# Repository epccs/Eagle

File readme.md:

# Eagle Circuit Board Files

Eagle is software for Computer Aided Design (CAD) of printed circuit boards. Eagle was once owned by a company from Germany called Cadsoft but is now owned by Autodesk (Autocad).

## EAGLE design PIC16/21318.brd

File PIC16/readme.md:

[PIC16]

This folder has the Eagle files for the PIC16 board.

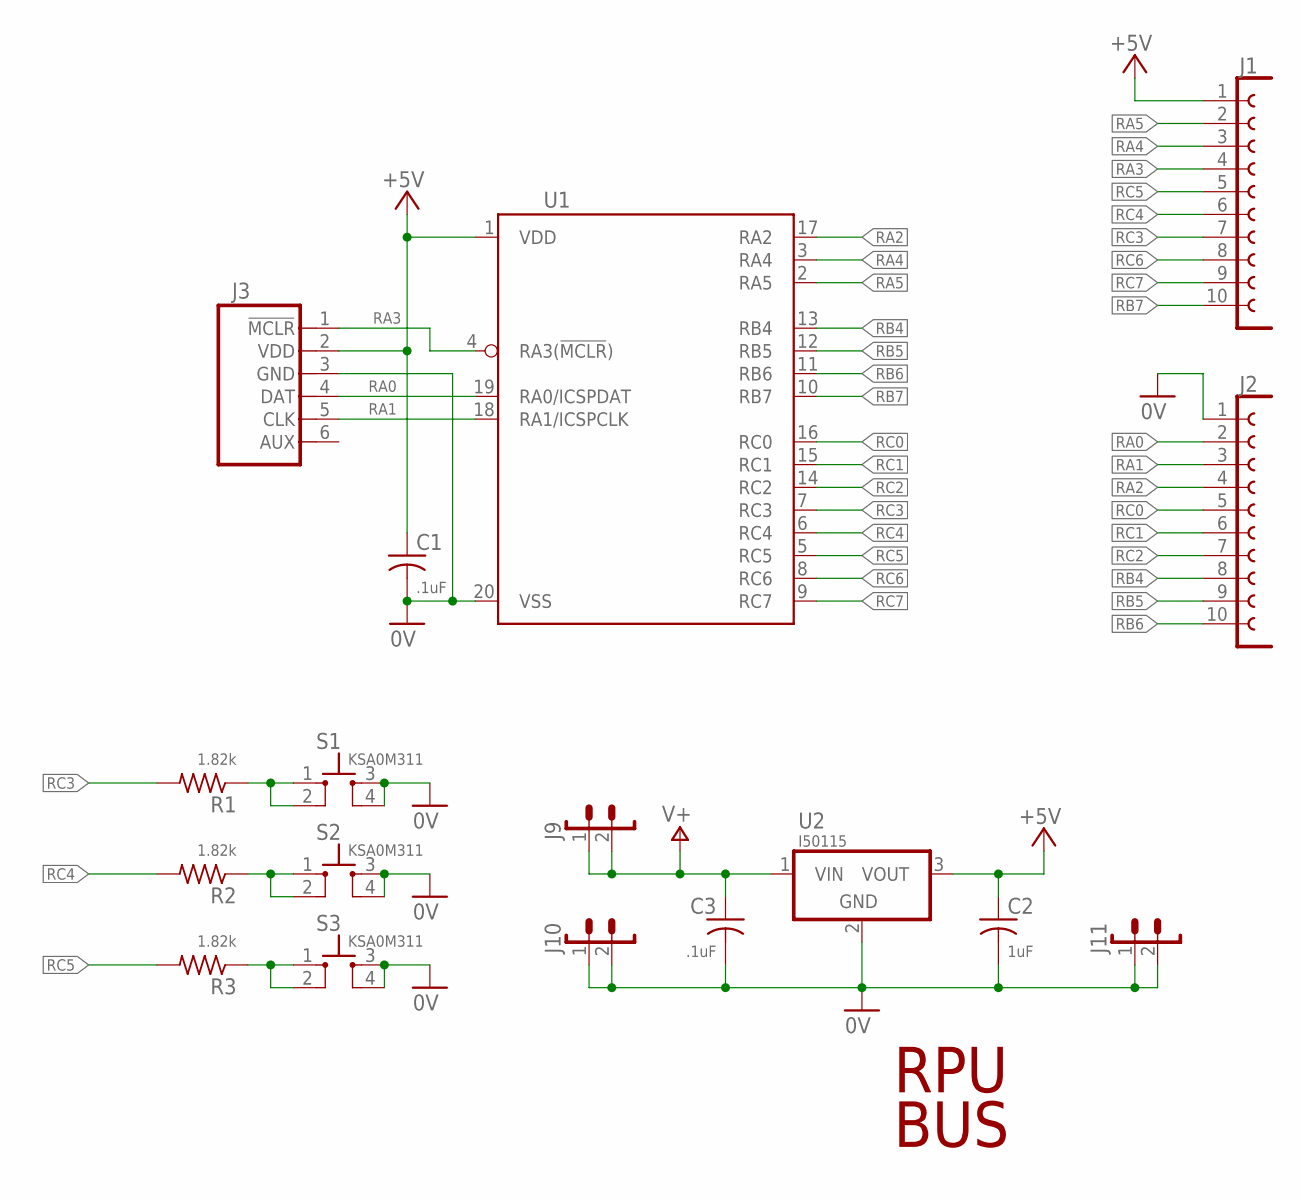
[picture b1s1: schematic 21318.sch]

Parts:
C1, C3: .1uF; C0603(1608)
C2: 1uF; C0805(2012)
J1, J2: F1X10
J3: ISP
J9, J10, J11: 1X2
R1, R2, R3: 1.82k; C0805(2012)
S1, S2, S3: KSA0M311; 0M311
U1: PIC16F18346-I/P; DIL20
U2: I50115; OKI-78SR-H

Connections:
0V: C1.2, C2.2, C3.2, J2.1, J3.3 (GND), J10.1, J10.2, J11.1, J11.2, S1.3, S1.4, S2.3, S2.4, S3.3, S3.4, U1.20 (VSS), U2.2 (GND)
+5V: C1.1, C2.1, J1.1, J3.2 (VDD), U1.1 (VDD), U2.3 (VOUT)
unnamed: R2.1, S2.1, S2.2
unnamed: R3.1, S3.1, S3.2
unnamed: R1.1, S1.1, S1.2
RA0: J2.2, J3.4 (DAT), U1.19 (RA0/ICSPDAT)
RA1: J2.3, J3.5 (CLK), U1.18 (RA1/ICSPCLK)
RA2: J2.4, U1.17 (RA2)
RA3: J1.4, J3.1 (!MCLR), U1.4 (RA3(!MCLR!))
RA4: J1.3, U1.3 (RA4)
RA5: J1.2, U1.2 (RA5)
RB4: J2.8, U1.13 (RB4)
RB5: J2.9, U1.12 (RB5)
RB6: J2.10, U1.11 (RB6)
RB7: J1.10, U1.10 (RB7)
RC0: J2.5, U1.16 (RC0)
RC1: J2.6, U1.15 (RC1)
RC2: J2.7, U1.14 (RC2)
RC3: J1.7, R1.2, U1.7 (RC3)
RC4: J1.6, R2.2, U1.6 (RC4)
RC5: J1.5, R3.2, U1.5 (RC5)
RC6: J1.8, U1.8 (RC6)
RC7: J1.9, U1.9 (RC7)
V+: C3.1, J9.1, J9.2, U2.1 (VIN)

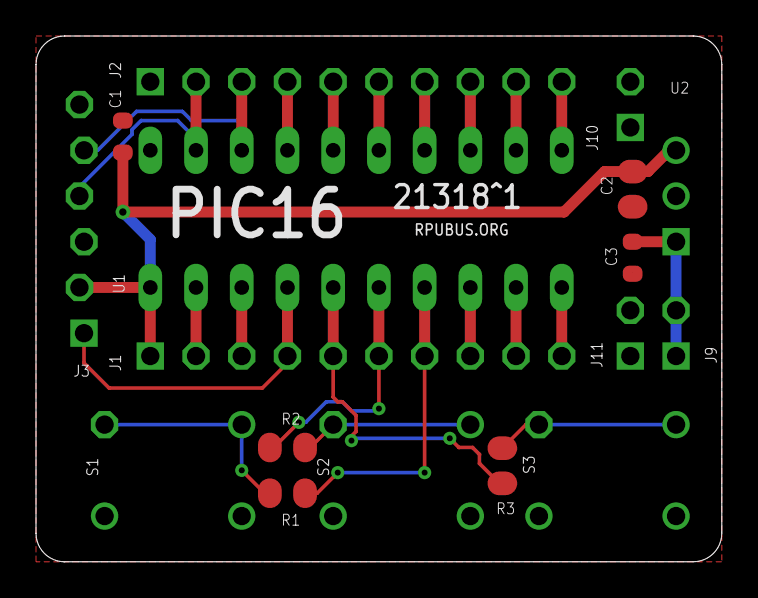
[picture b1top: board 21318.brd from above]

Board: 2 copper layers, 38.1 x 29.2 mm, 17 parts (0 on the bottom side), 24 nets.

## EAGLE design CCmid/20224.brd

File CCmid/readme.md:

CCmid

Constant current source based on AL8805W5-7 for LED or other uses. 

https://oshpark.com/shared_projects/9gUEmC1T

The alternat input of my control boards is for solar power, which acts as a constant current source. To charge from a regulated voltage source, the power needs to be converted through a CC source that is within the batteries charge ratting (e.g., <1/10 C, which is longer than 10 hour charging time) through the alternat input of on one of my boards. The alternat input will switch the CC source on and off, so a load dump needs to be handled with a TVS. 

Note: the lack of TVS on the Sparkfun boards is likely causing them problmes.

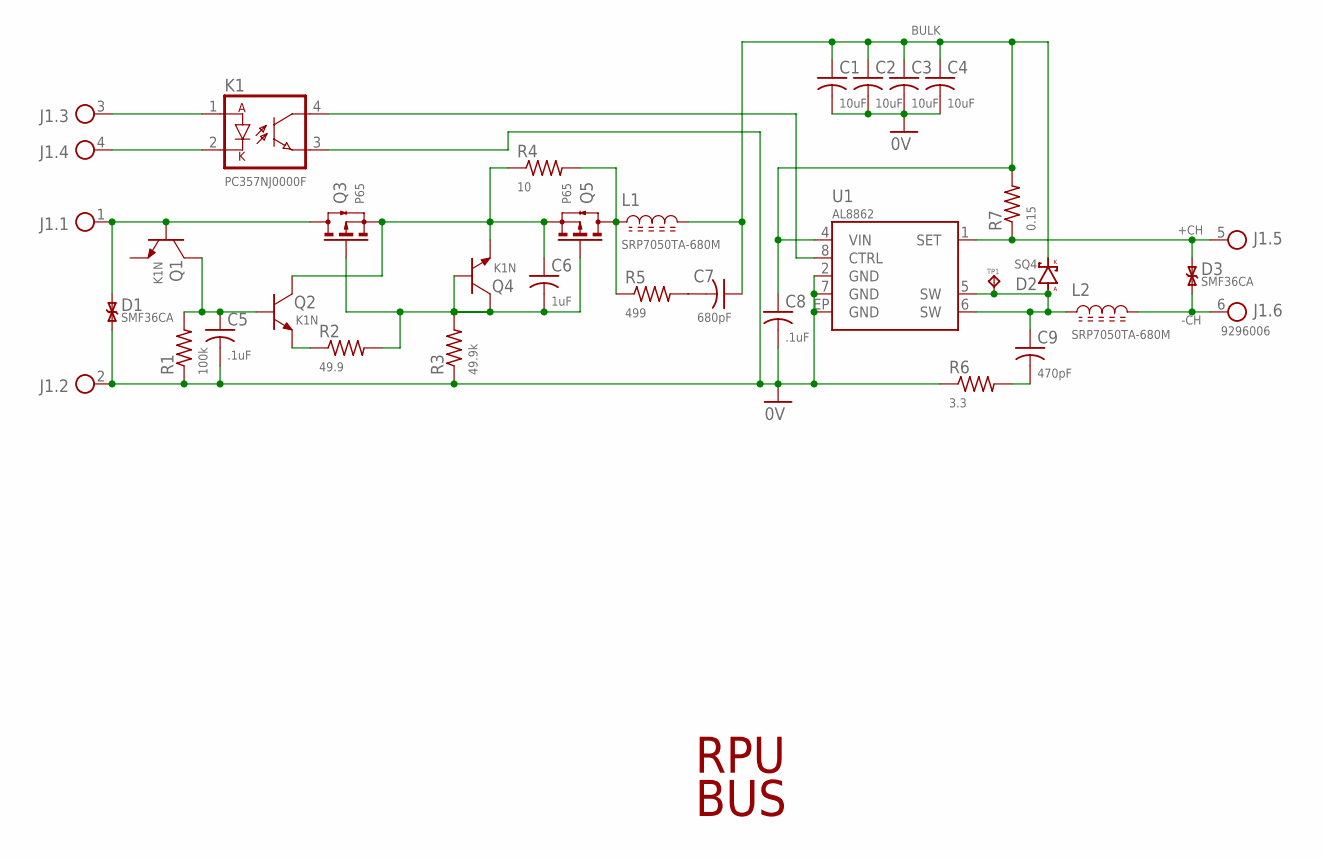
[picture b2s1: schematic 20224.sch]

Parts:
C1, C2, C3, C4: 10uF; C1206(3216)
C5, C8: .1uF; C0805(2012)
C6: 1uF; C0805(2012)
C7: 680pF; C0603(1608)
C9: 470pF; C0603(1608)
D1, D3: SMF36CA; SOD123
D2: SQ4; SMA
J1: 9296006; 06
K1: PC357NJ0000F; SMD4
L1, L2: SRP7050TA-680M; L2626
Q1, Q2, Q4: K1N; SOT23
Q3, Q5: P65; SOT23
R1: 100k; C0805(2012)
R2: 49.9; C0805(2012)
R3: 49.9k; C0805(2012)
R4: 10; C1206(3216)
R5: 499; C0805(2012)
R6: 3.3; C0805(2012)
R7: 0.15; C1210(3225)
TP1: TPPAD1-06; P1-06
U1: AL8862; SOIC8EP

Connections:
0V: C1.2, C2.2, C3.2, C4.2, C5.2, C8.2, D1.A, J1.2, K1.3 (E), R1.1, R3.1, R6.1, U1.2 (GND), U1.7 (GND), U1.EP (GND)
+CH: D3.C, J1.5, R7.1, U1.1 (SET)
-CH: D3.A, J1.6, L2.2
BULK: C1.1, C2.1, C3.1, C4.1, C7.1, C8.1, D2.K, L1.2, R7.2, U1.4 (VIN)
unnamed: K1.4 (C), U1.8 (CTRL)
unnamed: J1.3, K1.1 (A)
unnamed: C9.1, D2.A, L2.1, TP1.TP, U1.5 (SW), U1.6 (SW)
unnamed: J1.4, K1.2 (K)
unnamed: L1.1, Q5.3(D) (D), R4.2, R5.1
unnamed: C9.2, R6.2
unnamed: C7.2, R5.2
unnamed: D1.C, J1.1, Q1.B, Q3.3(D) (D)
unnamed: C5.1, Q1.C, Q2.B, R1.2
unnamed: Q2.E, R2.1
unnamed: C6.1, Q2.C, Q3.2(S) (S), Q4.E, Q5.2(S) (S), R4.1
unnamed: C6.2, Q3.1(G) (G), Q4.B, Q4.C, Q5.1(G) (G), R2.2, R3.2

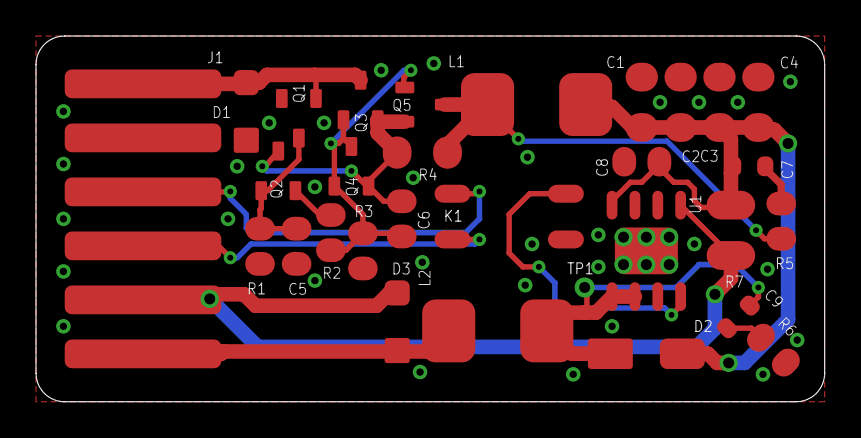
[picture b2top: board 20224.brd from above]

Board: 2 copper layers, 43.8 x 20.3 mm, 30 parts (0 on the bottom side), 16 nets.

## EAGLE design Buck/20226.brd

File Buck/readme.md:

Buck

Diodes AP64352Q wide input (8V to 40V) synchronous buck converter setup for output of 5V@3A. 

https://oshpark.com/shared_projects/UaJxkhrW

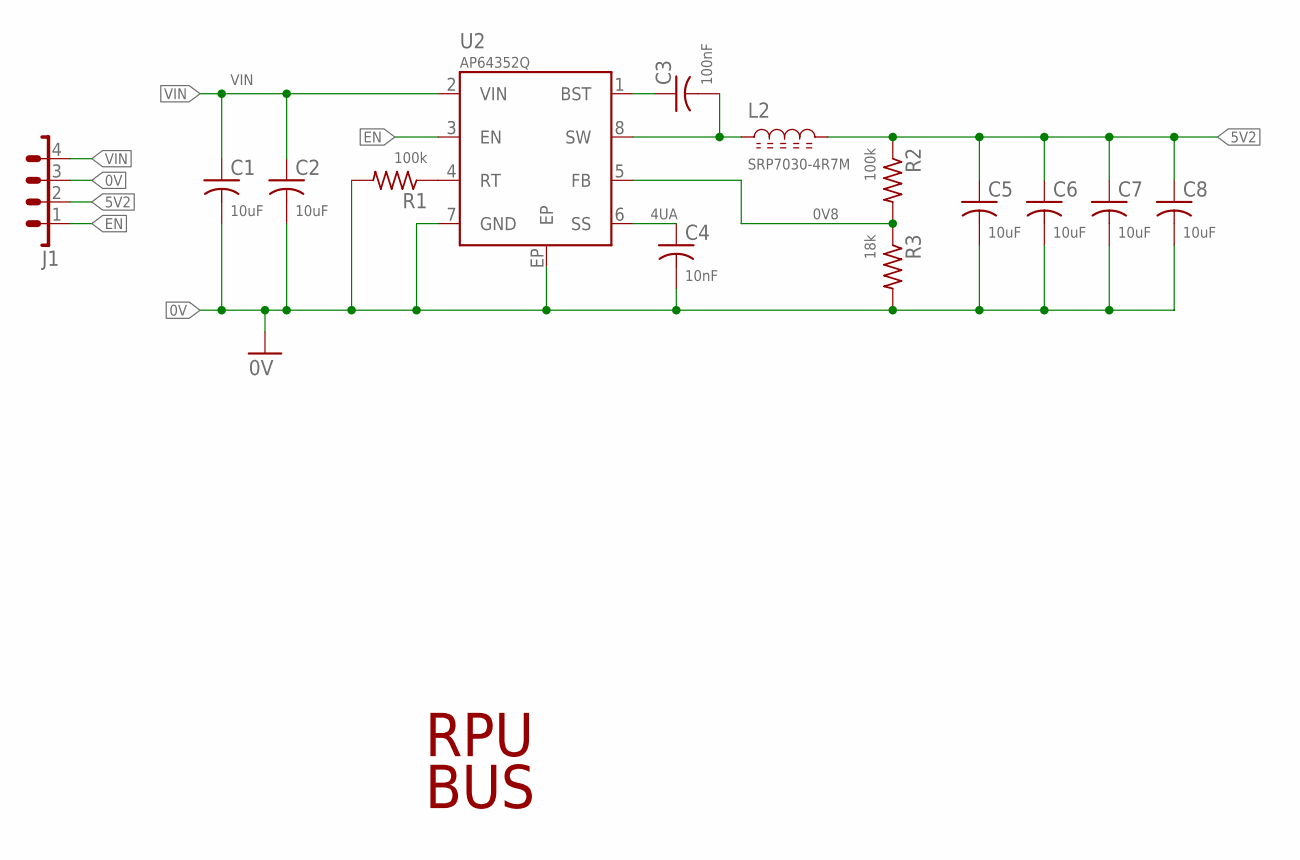
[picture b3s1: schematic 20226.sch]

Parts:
C1, C2, C5, C6, C7, C8: 10uF; C1206(3216)
C3: 100nF; C0603(1608)
C4: 10nF; C0603(1608)
J1: 1X4
L2: SRP7030-4R7M; L2831
R1, R2: 100k; C0805(2012)
R3: 18k; C0805(2012)
U2: AP64352Q; SOIC8EP

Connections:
0V: C1.2, C2.2, C4.2, C5.2, C6.2, C7.2, C8.2, J1.3, R1.2, R3.2, U2.7 (GND), U2.EP
0V8: R2.2, R3.1, U2.5 (FB)
4UA: C4.1, U2.6 (SS)
5V2: C5.1, C6.1, C7.1, C8.1, J1.2, L2.2, R2.1
EN: J1.1, U2.3 (EN)
unnamed: R1.1, U2.4 (RT)
unnamed: C3.1, U2.1 (BST)
unnamed: C3.2, L2.1, U2.8 (SW)
VIN: C1.1, C2.1, J1.4, U2.2 (VIN)

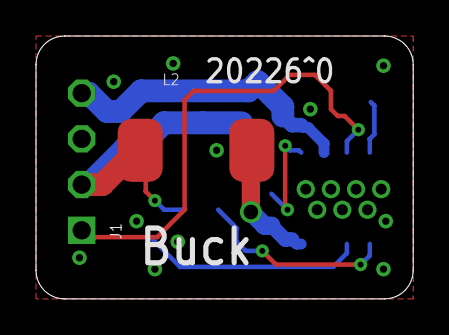
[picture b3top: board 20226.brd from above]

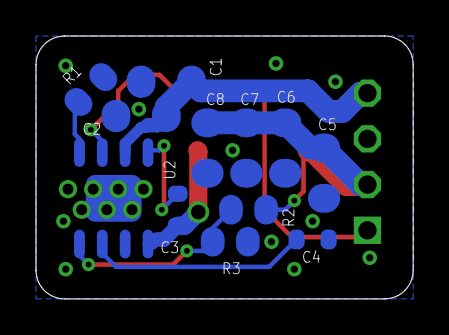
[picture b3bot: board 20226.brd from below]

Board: 2 copper layers, 21.0 x 14.6 mm, 14 parts (12 on the bottom side), 9 nets.

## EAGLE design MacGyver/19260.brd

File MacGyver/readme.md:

[MacGyver]

This folder has the Eagle files for the MacGyver board. To use it program the AVR128DB32 (manager) with UPDI from R-Pi header. Once the manager is programmed, the AVR128DA28 (application) can be programmed with UPDI over the multidrop serial from any connected host (e.g., other boards with an R-Pi or RPUusb).

[PiUpdi]: https://github.com/epccs/MacGyver/

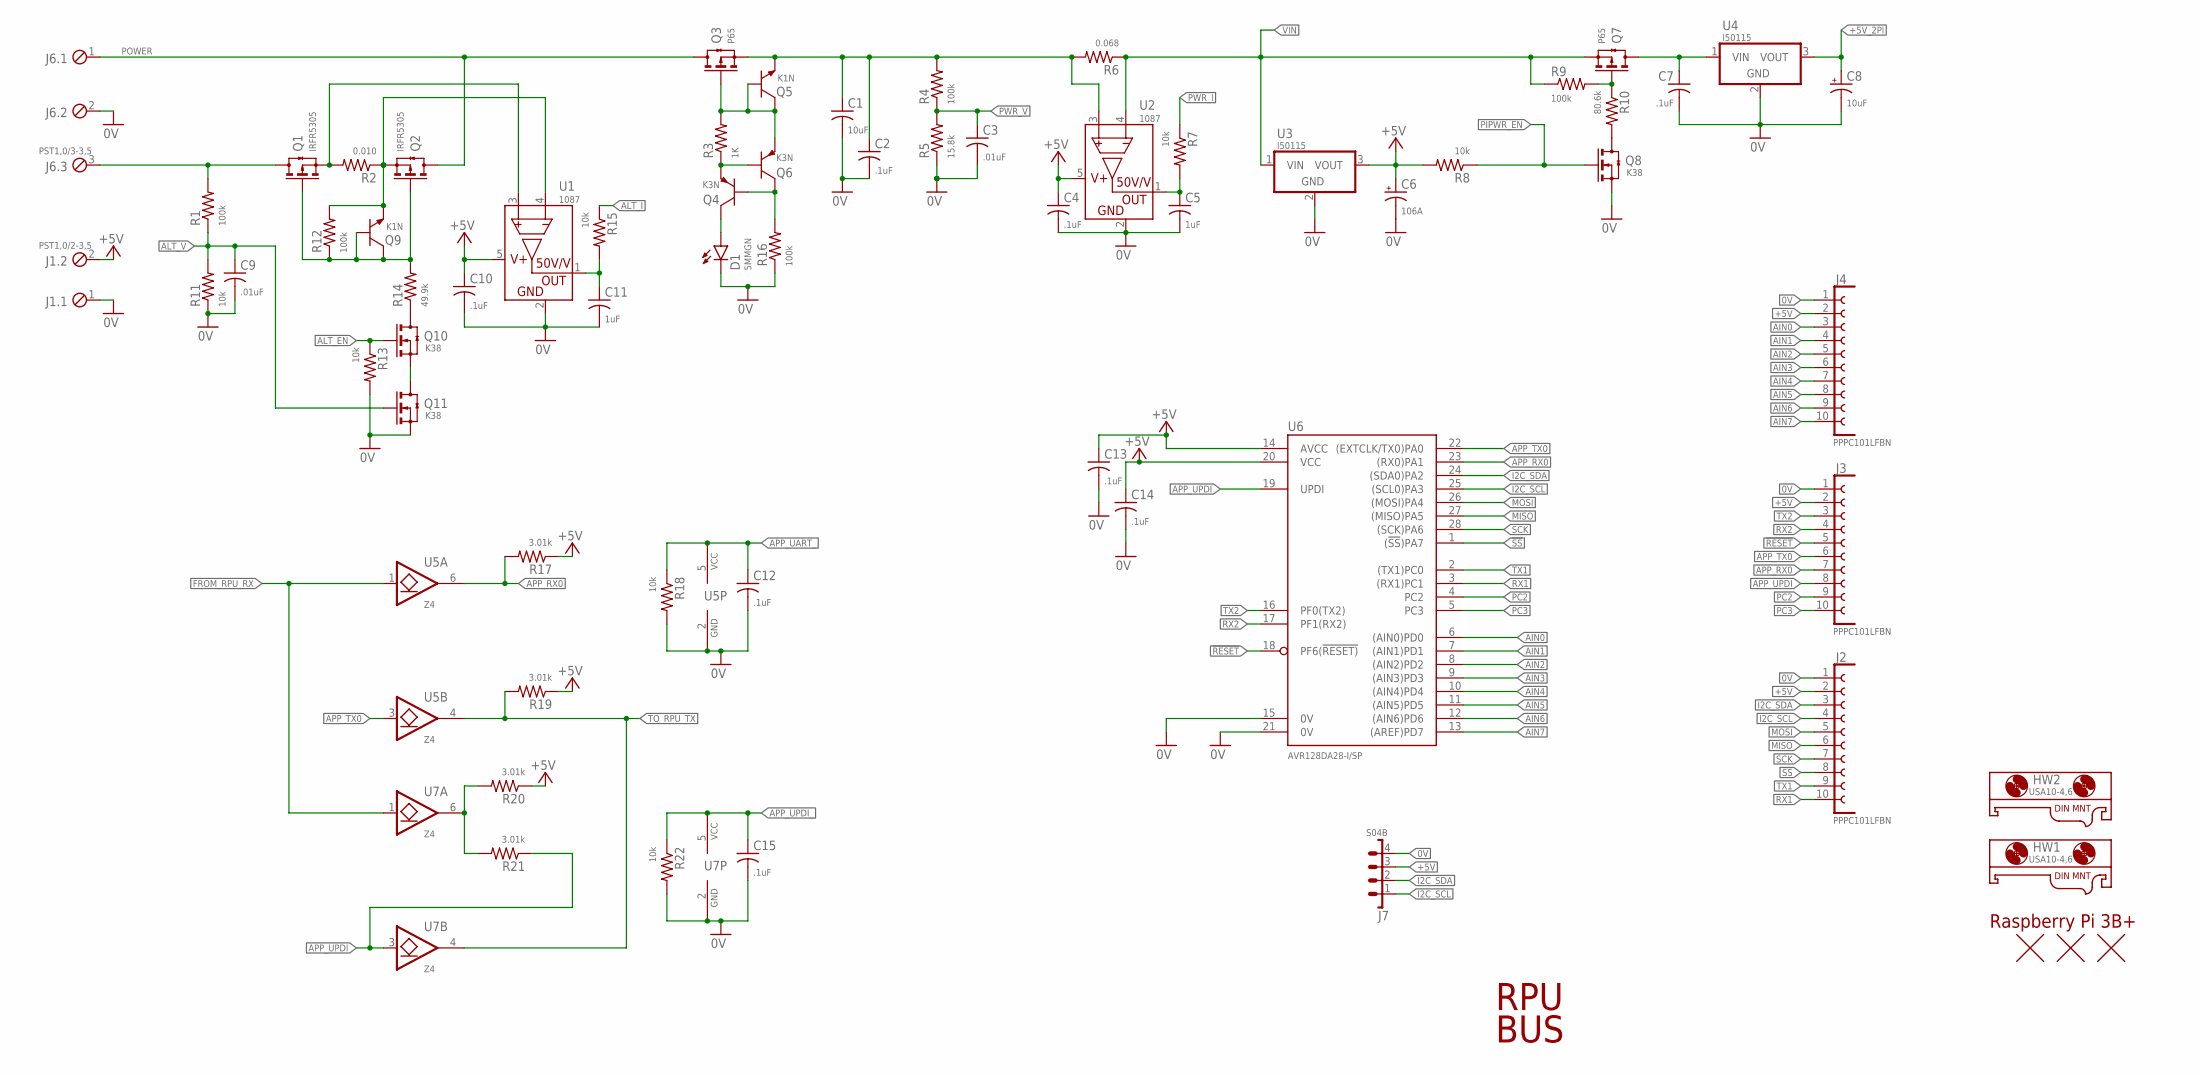
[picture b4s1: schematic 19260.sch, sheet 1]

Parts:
C1: 10uF; C1206(3216)
C2: .1uF; C0805(2012)
C3, C9: .01uF; C0603(1608)
C4, C7, C10, C12, C13, C14, C15: .1uF; C0603(1608)
C5, C11: 1uF; C0805(2012)
C6: 106A; 3216
C8: 10uF; 3216
D1: 5MMGN; LED5MM
HW1, HW2: USA10-4,6; USA10
J1: PST1,0/2-3,5; MCV2
J2, J3, J4: PPPC101LFBN; F1X10
J6: PST1,0/3-3,5; MCV3
J7: S04B; B04B
Q1, Q2: IRFR5305; DPAK
Q3, Q7: P65; SOT23
Q4, Q6: K3N; SOT23
Q5, Q9: K1N; SOT23
Q8, Q10, Q11: K38; SOT23
R1, R4, R9, R12, R16: 100k; C0805(2012)
R2: 0.010; C1210(3225)
R3: 1K; C0805(2012)
R5: 15.8k; C0805(2012)
R6: 0.068; C1210(3225)
R7, R8, R11, R13, R15, R18, R22: 10k; C0805(2012)
R10: 80.6k; C0805(2012)
R14: 49.9k; C0805(2012)
R17, R19, R20, R21: 3.01k; C0805(2012)
U1, U2: 1087; SOT23-5
U3, U4: I50115; OKI-78SR-H
U5, U7: Z4; SOT23-6,SOT26
U6: AVR128DA28-I/SP; DIL28-3
U$1: R-PI3B+
U$2, U$3, U$4: FIDUCIAL1.27; FIDUCIAL-1.27

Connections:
0V: C1.2, C2.2, C3.2, C4.2, C5.2, C6.-, C7.2, C8.-, C9.2, C10.2, C11.2, C12.2, C13.2, C14.2, C15.2, D1.K, J1.1, J2.1, J3.1, J4.1, J6.2, J7.4, Q8.2(S) (S), Q11.2(S) (S), R5.1, R11.1, R13.2, R16.1, R18.2, R22.2, U1.2 (GND), U2.2 (GND), U3.2 (GND), U4.2 (GND), U5.2 (GND), U6.15 (0V), U6.21 (0V), U7.2 (GND); also elsewhere on the board
!RESET: J3.5, U6.18 (PF6(!RESET))
!SS: J2.8, U6.1 ((!SS!)PA7)
+5V: C4.1, C6.+, C10.1, C13.1, C14.1, J1.2, J2.2, J3.2, J4.2, J7.3, R8.2, R17.1, R19.1, R20.1, U1.5 (VCC), U2.5 (VCC), U3.3 (VOUT), U6.14 (AVCC), U6.20 (VCC); also elsewhere on the board
+5V_2PI: C8.+, U4.3 (VOUT); also elsewhere on the board
AIN0: J4.3, U6.6 ((AIN0)PD0)
AIN1: J4.4, U6.7 ((AIN1)PD1)
AIN2: J4.5, U6.8 ((AIN2)PD2)
AIN3: J4.6, U6.9 ((AIN3)PD3)
AIN4: J4.7, U6.10 ((AIN4)PD4)
AIN5: J4.8, U6.11 ((AIN5)PD5)
AIN6: J4.9, U6.12 ((AIN6)PD6)
AIN7: J4.10, U6.13 ((AREF)PD7)
ALT_EN: Q10.1(G) (G), R13.1; also elsewhere on the board
ALT_I: R15.1; also elsewhere on the board
ALT_V: C9.1, Q11.1(G) (G), R1.1, R11.2; also elsewhere on the board
APP_RX0: J3.7, R17.2, U5.6 (O), U6.23 ((RX0)PA1)
APP_TX0: J3.6, U5.3 (I), U6.22 ((EXTCLK/TX0)PA0)
APP_UART_: C12.1, R18.1, U5.5 (VCC); also elsewhere on the board
APP_UPDI: J3.8, R21.1, U6.19 (UPDI), U7.3 (I)
APP_UPDI_: C15.1, R22.1, U7.5 (VCC); also elsewhere on the board
APP_UPDI_PULLUP: R20.2, R21.2, U7.6 (O)
FROM_RPU_RX: U5.1 (I), U7.1 (I); also elsewhere on the board
I2C_SCL: J2.4, J7.1, U6.25 ((SCL0)PA3); also elsewhere on the board
I2C_SDA: J2.3, J7.2, U6.24 ((SDA0)PA2); also elsewhere on the board
MISO: J2.6, U6.27 ((MISO)PA5)
MOSI: J2.5, U6.26 ((MOSI)PA4)
unnamed: Q7.1(G) (G), R9.2, R10.1
unnamed: Q8.3(D) (D), R10.2
unnamed: Q4.B, Q6.C, R16.2
unnamed: Q3.1(G) (G), Q5.B, Q5.C, Q6.E, R3.2
unnamed: D1.A, Q4.C
unnamed: C5.1, R7.2, U2.1 (OUT)
unnamed: Q4.E, Q6.B, R3.1
unnamed: J6.3, Q1.SINK (D), R1.2
unnamed: Q2.3 (S), Q9.E, R2.1, R12.2, U1.4 (S-)
unnamed: Q1.1 (G), Q2.1 (G), Q9.B, Q9.C, R12.1, R14.2
unnamed: Q10.3(D) (D), R14.1
unnamed: C11.1, R15.2, U1.1 (OUT)
unnamed: Q1.3 (S), R2.2, U1.3 (S+)
unnamed: Q10.2(S) (S), Q11.3(D) (D)
PC2: J3.9, U6.4 (PC2)
PC3: J3.10, U6.5 (PC3)
PIPWR_EN: Q8.1(G) (G), R8.1; also elsewhere on the board
POWER: J6.1, Q2.SINK (D), Q3.3(D) (D)
PWR_I: R7.1; also elsewhere on the board
PWR_V: C3.1, R4.1, R5.2; also elsewhere on the board
RX1: J2.10, U6.3 ((RX1)PC1)
RX2: J3.4, U6.17 (PF1(RX2))
SCK: J2.7, U6.28 ((SCK)PA6)
SHLD_VIN: C7.1, Q7.3(D) (D), U4.1 (VIN)
TO_RPU_TX: R19.2, U5.4 (O), U7.4 (O); also elsewhere on the board
TX1: J2.9, U6.2 ((TX1)PC0)
TX2: J3.3, U6.16 (PF0(TX2))
VIN: Q7.2(S) (S), R6.1, R9.1, U2.4 (S-), U3.1 (VIN)
VIN_S: C1.1, C2.1, Q3.2(S) (S), Q5.E, R4.2, R6.2, U2.3 (S+)

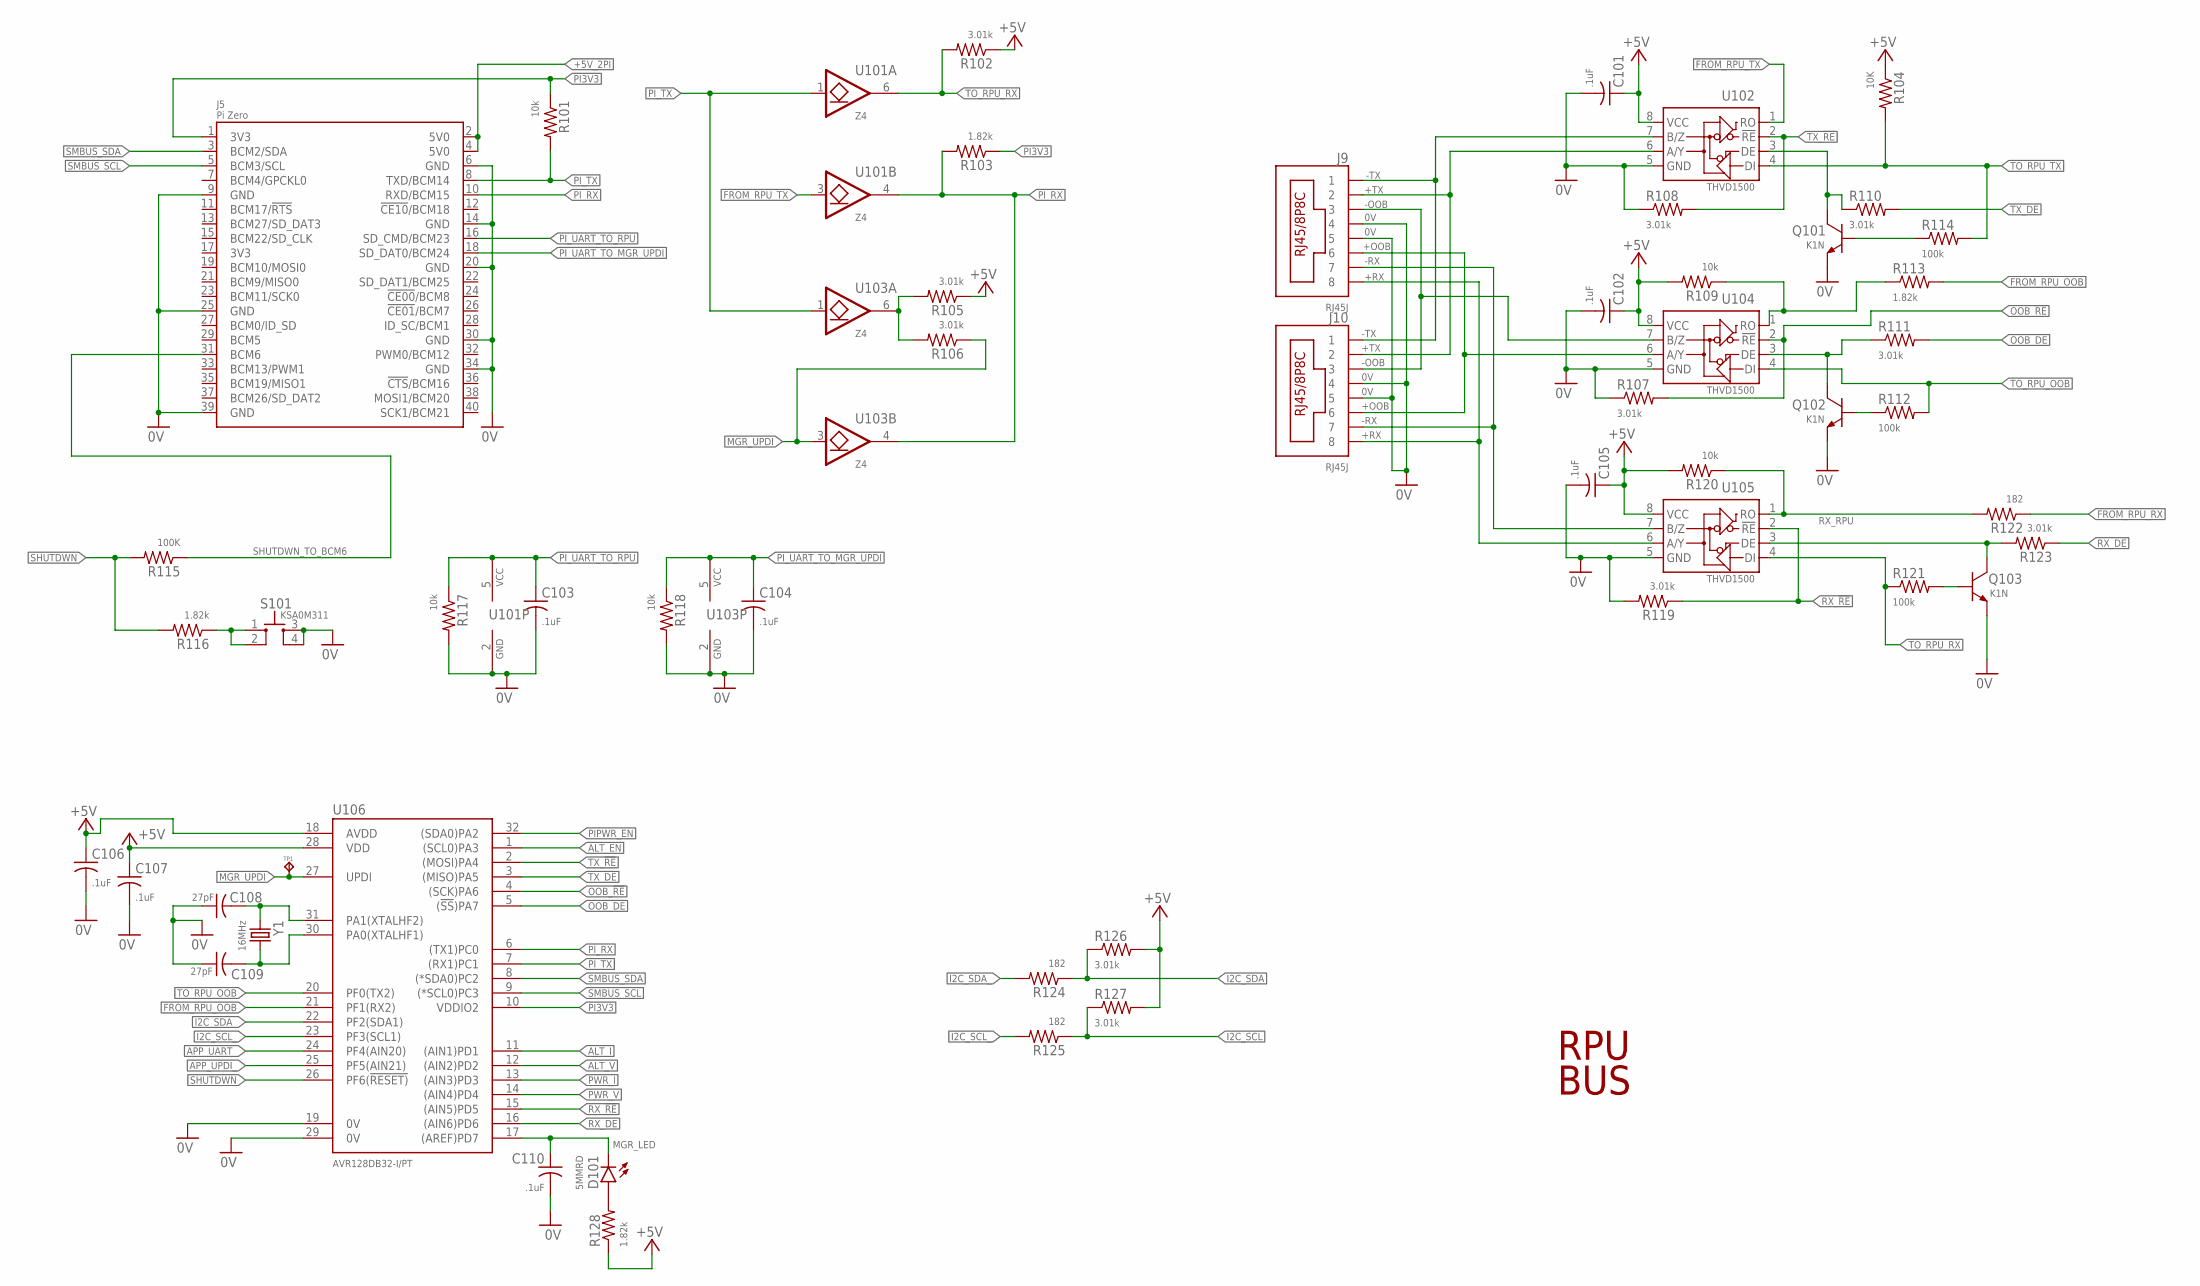
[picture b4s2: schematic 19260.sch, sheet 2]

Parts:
C101, C102, C103, C104, C105, C106, C107, C110: .1uF; C0603(1608)
C108, C109: 27pF; C0603(1608)
D101: 5MMRD; LED5MM
J5: Pi Zero; RASPI_ZERO_V40PIN
J9, J10: RJ45J; RJ45-8HZT
Q101, Q102, Q103: K1N; SOT23
R101, R109, R117, R118, R120: 10k; C0805(2012)
R102, R105, R106, R107, R108, R110, R111, R119, R123, R126, R127: 3.01k; C0805(2012)
R103, R113, R116, R128: 1.82k; C0805(2012)
R104: 10K; C0805(2012)
R112, R114, R121: 100k; C0805(2012)
R115: 100K; C0805(2012)
R122, R124, R125: 182; C0805(2012)
S101: KSA0M311; 0M311
TP1: TPPAD1-08; P1-08
U101, U103: Z4; SOT23-6,SOT26
U102, U104, U105: THVD1500; SOIC8
U106: AVR128DB32-I/PT; TQFP32-08
Y1: 16MHz; CSM-3X

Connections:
0V: C101.2, C102.2, C103.2, C104.2, C105.2, C106.2, C107.2, C108.1, C109.1, C110.2, J5.6 (GND), J5.9 (GND), J5.14 (GND), J5.20 (GND), J5.25 (GND), J5.30 (GND), J5.34 (GND), J5.39 (GND), J9.4, J9.5, J10.4, J10.5, Q101.E, Q102.E, Q103.E, R107.1, R108.1, R117.2, R118.2, R119.2, S101.3, S101.4, U101.2 (GND), U102.5 (GND), U103.2 (GND), U104.5 (GND), U105.5 (GND), U106.19 (0V), U106.29 (0V); also elsewhere on the board
+5V: C101.1, C102.1, C105.1, C106.1, C107.1, R102.1, R104.1, R105.1, R109.2, R120.2, R126.2, R127.2, R128.1, U102.8 (VCC), U104.8 (VCC), U105.8 (VCC), U106.18 (AVDD), U106.28 (VDD); also elsewhere on the board
+5V_2PI: J5.2 (5V0), J5.4 (5V0); also elsewhere on the board
+OOB: J9.6, J10.6, U104.6 (A/Y)
+RX: J9.8, J10.8, U105.6 (A/Y)
+TX: J9.2, J10.2, U102.6 (A/Y)
-OOB: J9.3, J10.3, U104.7 (B/Z)
-RX: J9.7, J10.7, U105.7 (B/Z)
-TX: J9.1, J10.1, U102.7 (B/Z)
ALT_EN: U106.1 ((SCL0)PA3); also elsewhere on the board
ALT_I: U106.11 ((AIN1)PD1); also elsewhere on the board
ALT_V: U106.12 ((AIN2)PD2); also elsewhere on the board
APP_UART_: U106.24 (PF4(AIN20)); also elsewhere on the board
APP_UPDI_: U106.25 (PF5(AIN21)); also elsewhere on the board
FROM_RPU_OOB: R113.2, U106.21 (PF1(RX2))
FROM_RPU_RX: R122.1; also elsewhere on the board
FROM_RPU_TX: U101.3 (I), U102.1 (RO)
I2C_SCL: R125.1, R127.1; also elsewhere on the board
I2C_SCL_: R125.2, U106.23 (PF3(SCL1))
I2C_SDA: R124.1, R126.1; also elsewhere on the board
I2C_SDA_: R124.2, U106.22 (PF2(SDA1))
MGR_LED: C110.1, D101.K, U106.17 ((AREF)PD7)
MGR_UPDI: R106.1, TP1.TP, U103.3 (I), U106.27 (UPDI)
MGR_UPDI_PULLUP: R105.2, R106.2, U103.6 (O)
unnamed: C108.2, U106.31 (PA1(XTALHF2)), Y1.1
unnamed: C109.2, U106.30 (PA0(XTALHF1)), Y1.2
unnamed: Q101.B, R114.1
unnamed: Q101.C, R110.1, U102.3 (DE)
unnamed: R109.1, R113.1, U104.1 (RO)
unnamed: Q102.C, R111.1, U104.3 (DE)
unnamed: Q102.B, R112.1
unnamed: Q103.B, R121.2
unnamed: D101.A, R128.2
unnamed: Q103.C, R123.2, U105.3 (DE)
unnamed: R116.1, S101.1, S101.2
OOB_!RE: R107.2, U104.2 (!RE), U106.4 ((SCK)PA6)
OOB_DE: R111.2, U106.5 ((!SS!)PA7)
PI3V3: J5.1 (3V3), R101.1, R103.1, U106.10 (VDDIO2)
PIPWR_EN: U106.32 ((SDA0)PA2); also elsewhere on the board
PI_RX: J5.10 (RXD/BCM15), R103.2, U101.4 (O), U103.4 (O), U106.6 ((TX1)PC0)
PI_TX: J5.8 (TXD/BCM14), R101.2, U101.1 (I), U103.1 (I), U106.7 ((RX1)PC1)
PI_UART_TO_MGR_UPDI: C104.1, J5.18 (SD_DAT0/BCM24), R118.1, U103.5 (VCC)
PI_UART_TO_RPU: C103.1, J5.16 (SD_CMD/BCM23), R117.1, U101.5 (VCC)
PWR_I: U106.13 ((AIN3)PD3); also elsewhere on the board
PWR_V: U106.14 ((AIN4)PD4); also elsewhere on the board
RX_!RE: R119.1, U105.2 (!RE), U106.15 ((AIN5)PD5)
RX_DE: R123.1, U106.16 ((AIN6)PD6)
RX_RPU: R120.1, R122.2, U105.1 (RO)
SHUTDWN: R115.2, R116.2, U106.26 (PF6(!RESET))
SHUTDWN_TO_BCM6: J5.31 (BCM6), R115.1
SMBUS_SCL: J5.5 (BCM3/SCL), U106.9 ((*SCL0)PC3)
SMBUS_SDA: J5.3 (BCM2/SDA), U106.8 ((*SDA0)PC2)
TO_RPU_OOB: R112.2, U104.4 (DI), U106.20 (PF0(TX2))
TO_RPU_RX: R102.2, R121.1, U101.6 (O), U105.4 (DI)
TO_RPU_TX: R104.2, R114.2, U102.4 (DI); also elsewhere on the board
TX_!RE: R108.2, U102.2 (!RE), U106.2 ((MOSI)PA4)
TX_DE: R110.2, U106.3 ((MISO)PA5)

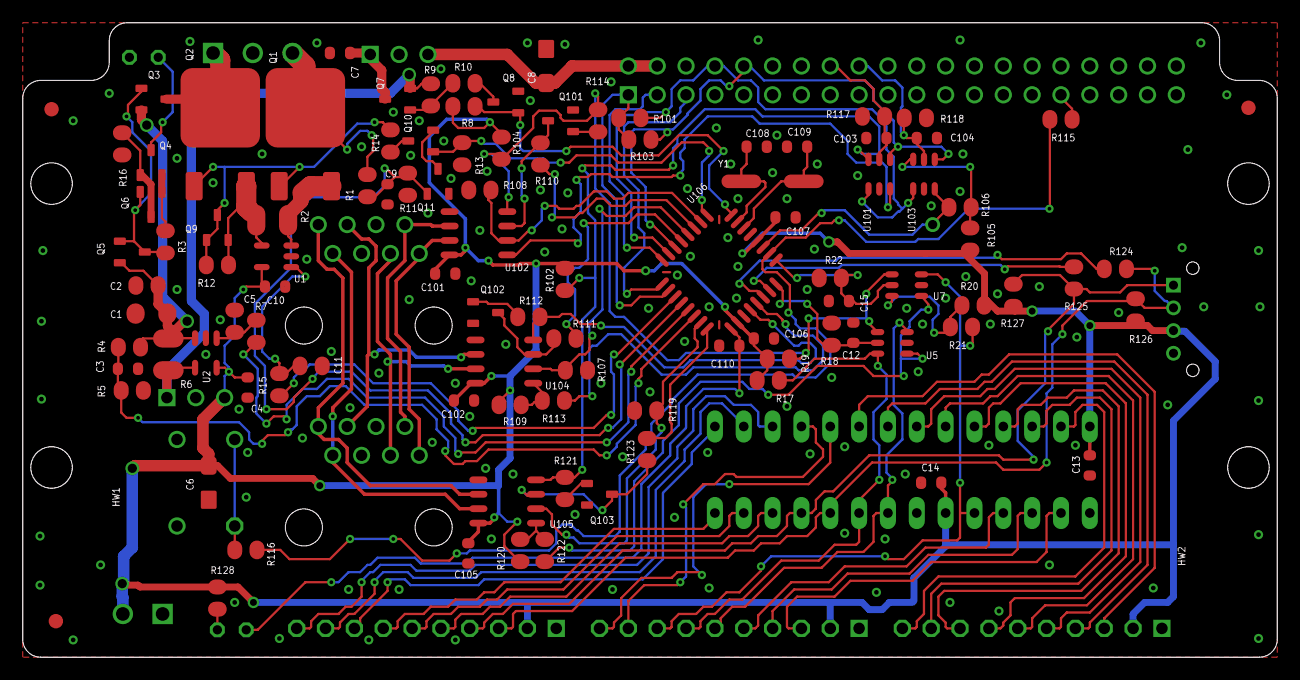
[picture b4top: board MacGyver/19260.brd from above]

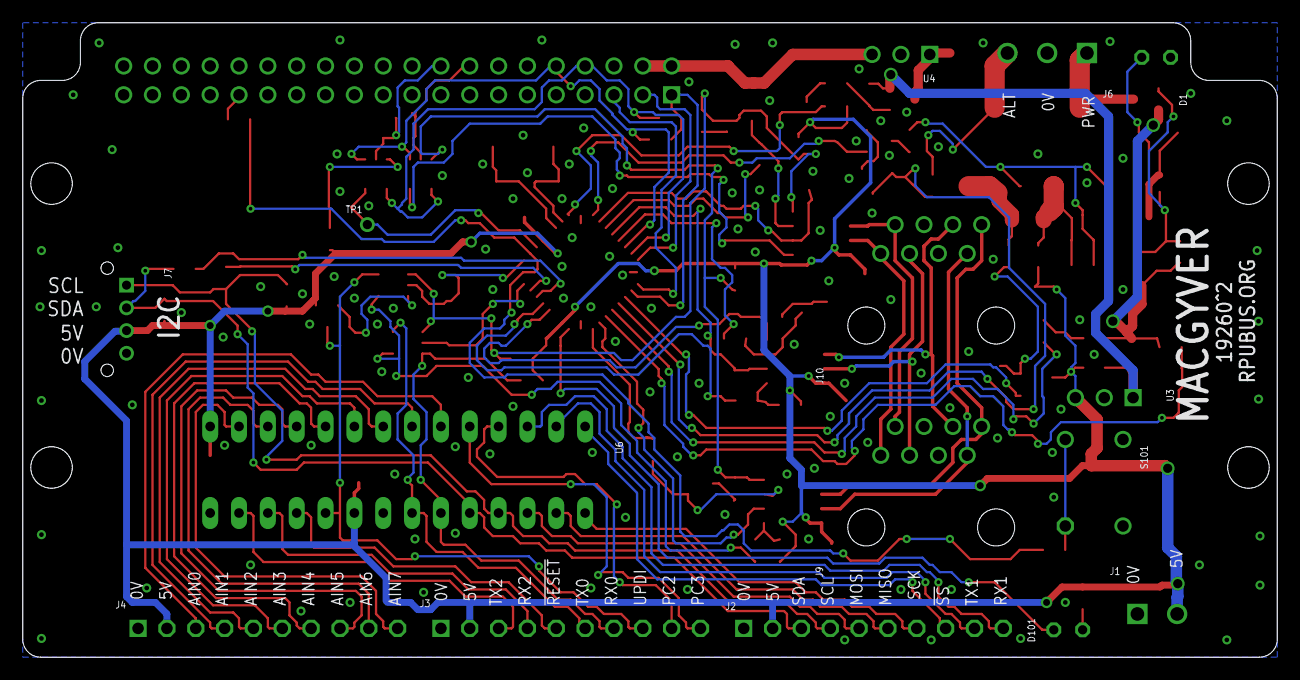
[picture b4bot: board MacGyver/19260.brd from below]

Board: 2 copper layers, 110.5 x 55.9 mm, 122 parts (17 on the bottom side), 98 nets.

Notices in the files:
parts and their libraries:
R-C: Copyright (C) 2013 Ronald Steven Sutherland
under the terms of the GNU Free Documentation License, Version 1.2 or
any later version published by the Free Software Foundation; with no
U-Linear: Copyright (C) 2014 Ronald Steven Sutherland
Released under the Creative Commons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
